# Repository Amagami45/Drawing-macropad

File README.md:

# Drawing-macropad
This is my ultimate drawing macropad.

##  Hardware Overview

### Components
- Seeed Studio XIAO RP2040  
- EC11 rotary encoder with push switch  
- 128×32 OLED  
- 5× mechanical switches  

### Features
- Zoom in/out using the encoder  
- Reset zoom with encoder button  
- Undo / Redo / Brush / Eraser / Color Picker keys  
- OLED shows current action (Zoom +, Undo, Brush, etc.)

##  Firmware (CircuitPython)

The macropad runs on **CircuitPython**.

### Default Controls
- **Encoder Clockwise:** Zoom In (`CTRL +`)
- **Encoder Counter‑Clockwise:** Zoom Out (`CTRL -`)
- **Encoder Button:** Reset Zoom (`CTRL 0`)
- **Key 1:** Undo (`CTRL Z`)
- **Key 2:** Redo(`CTRL Y`)
- **Key 3:** Brush
- **Key 4:** Eraser
- **Key 5:** Color Picker

The OLED displays the current action.
### Bill of Materials (BOM)
- 1× Seeed Studio XIAO RP2040  
- 1× EC11 encoder
- 1× OLED displey
- 5× switches
- 5× keycaps 
- 4× M3 screws 
- 1× own PCB  

##  Screenshots

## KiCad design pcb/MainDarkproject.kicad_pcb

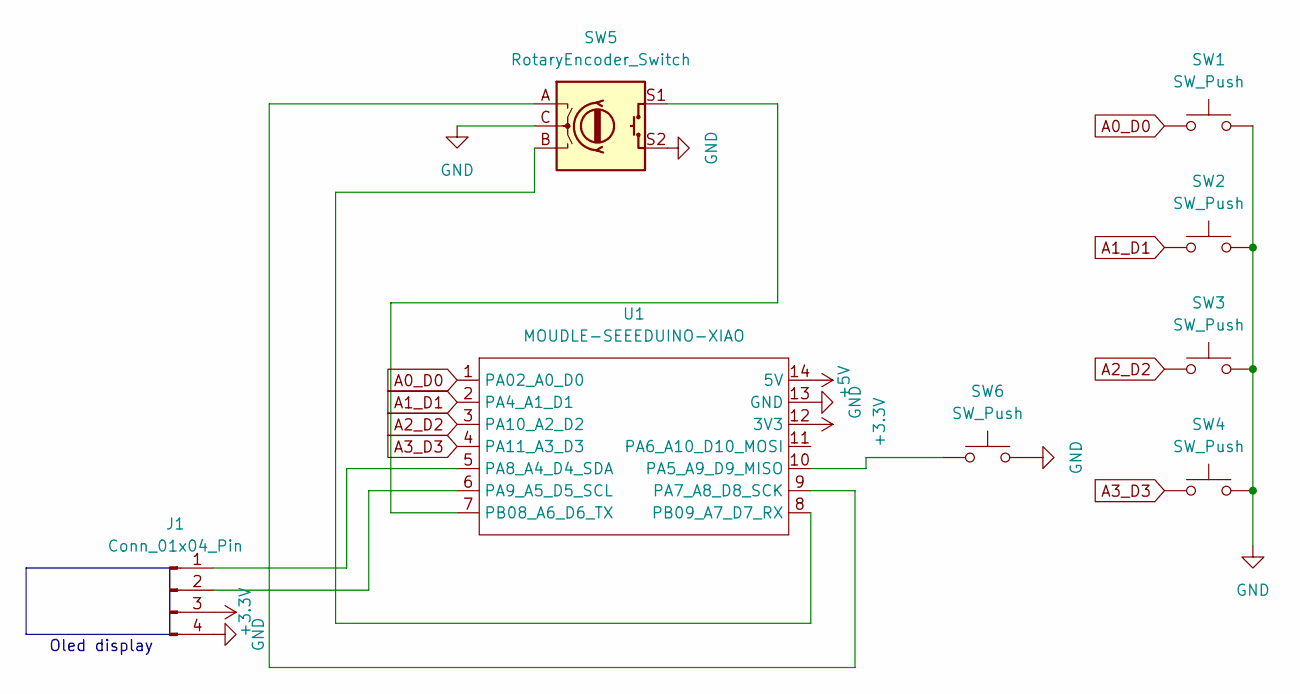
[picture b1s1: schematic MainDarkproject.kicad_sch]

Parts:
J1: Conn_01x04_Pin; SSD1306-0.91-OLED-4pin-128x32 (1)
SW1, SW2, SW3, SW4, SW6: SW_Push; SW_Cherry_MX_1.00u_PCB
SW5: RotaryEncoder_Switch; RotaryEncoder_Alps_EC11E-Switch_Vertical_H20mm
U1: MOUDLE-SEEEDUINO-XIAO; XIAO-Generic-Hybrid-14P-2.54-21X17.8MM

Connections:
+3.3V: J1.3, U1.12 (3V3)
+5V: U1.14 (5V)
A0_D0: SW1.1, U1.1 (PA02_A0_D0)
A1_D1: SW2.1, U1.2 (PA4_A1_D1)
A2_D2: SW3.1, U1.3 (PA10_A2_D2)
A3_D3: SW4.1, U1.4 (PA11_A3_D3)
GND: J1.4, SW1.2, SW2.2, SW3.2, SW4.2, SW5.C, SW5.S2, SW6.2, U1.13 (GND)
unnamed: J1.1, U1.5 (PA8_A4_D4_SDA)
unnamed: J1.2, U1.6 (PA9_A5_D5_SCL)
unnamed: SW6.1, U1.10 (PA5_A9_D9_MISO)
unnamed: SW5.A, U1.9 (PA7_A8_D8_SCK)
unnamed: SW5.S1, U1.7 (PB08_A6_D6_TX)
unnamed: SW5.B, U1.8 (PB09_A7_D7_RX)

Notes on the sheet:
Oled display

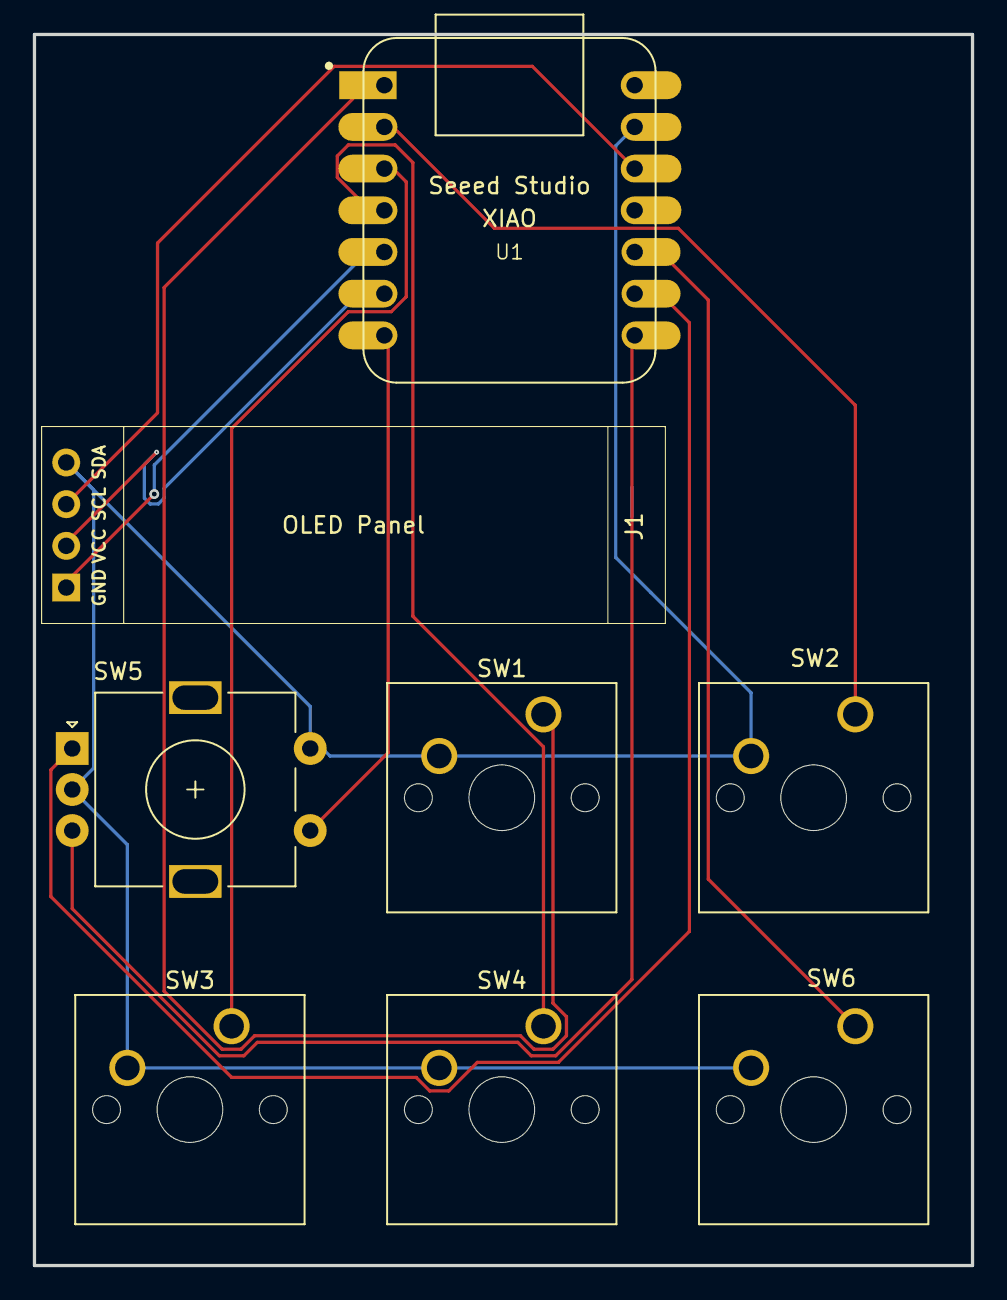
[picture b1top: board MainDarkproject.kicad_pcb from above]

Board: 2 copper layers, 57.1 x 75.0 mm, 8 parts (0 on the bottom side), 12 nets.
